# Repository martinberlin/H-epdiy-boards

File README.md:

## H-epdiy-boards list of open source variations

This boards where made with collaboration from Larry Bank and support from the [NLnet foundation](https://nlnet.nl).
Each variation is targeted for different needs. Intended for everyone to make their own custom modifications. For example: You don't need one of the eink connectors, or you don't need RTC, then just remove it from the Pick and place order. For more advanced users you can of course open the board in KiCad and reorganize stuff.
Pull Requests with variations or fixes are welcome.
Any of this circuits is made or designed with AI. They are all human reviewed and crafted carefully.

### epdiy-model-F

**What it provides:**

- A 40 pin connector for 16 bit Eink displays like ED103TC2 or ED103MC2
- 8 free GPIOs exposed if you don't use the 16 bit display
- A 34 pin connector for 8 bit Kindle like Eink displays (All the ED060***)
- Double USB-C connector w/built in USB only (no UART)
- A single BOOT / USER button (IO 0)
- An IR receiver TSOP341 (LCSC: C118303)
- RV3032 RTC with the INT pin connected to IO3 (RTC GPIO so you can wake up the MCU)
- Switchable QWIIC power so you can switch on a peripheral and cut it's power completely
- TP4056 battery charger

The IR is meant so you can make a simple Firmware and change the display content with  your TV remote.

How it looks like:

Some features like RTC and IR receiver:

[Full schematics PDF](epdiy-v7-model-F/v7-model-f_1.0.pdf)

## Links of interest

[How to read codes from IR Remote controls](https://bitbanksoftware.blogspot.com/2026/11/how-to-read-codes-from-many-ir-remote.html) Good article from Larry about receiving IR codes

[IDF Nec IR receive example](https://github.com/espressif/esp-idf/tree/master/examples/peripherals/rmt/ir_nec_transceiver) if you like ESP-IDF, just set the RX pin in **main/ir_nec_transceiver_main.c** to 43, make a **set-target esp32s3** and you are ready for an **idf.py flash monitor**

[sensoria board](https://fasani.de/2026/01/16/new-product-and-service-launched-sensoria/) A new product we are launching with a 5.2 inch variation of a FastEPD board

[FastEPD](https://github.com/bitbank2/FastEPD) An alternative and different library than epdiy to control raw parallel eink displays

If anyone makes a great Firmware to interact with an online image gallery and receive IR commands, then he can claim a 50% discount and free shipping in any of my boards sold on Tindie (I will send a Coupon)
PRE-REQUISITES: It should be code by hand with carefully clean code. Detection that is made with Claude or any other AI coding tool leaves you out of the contest.  You need to provide proof of commit history exactly for that reason.

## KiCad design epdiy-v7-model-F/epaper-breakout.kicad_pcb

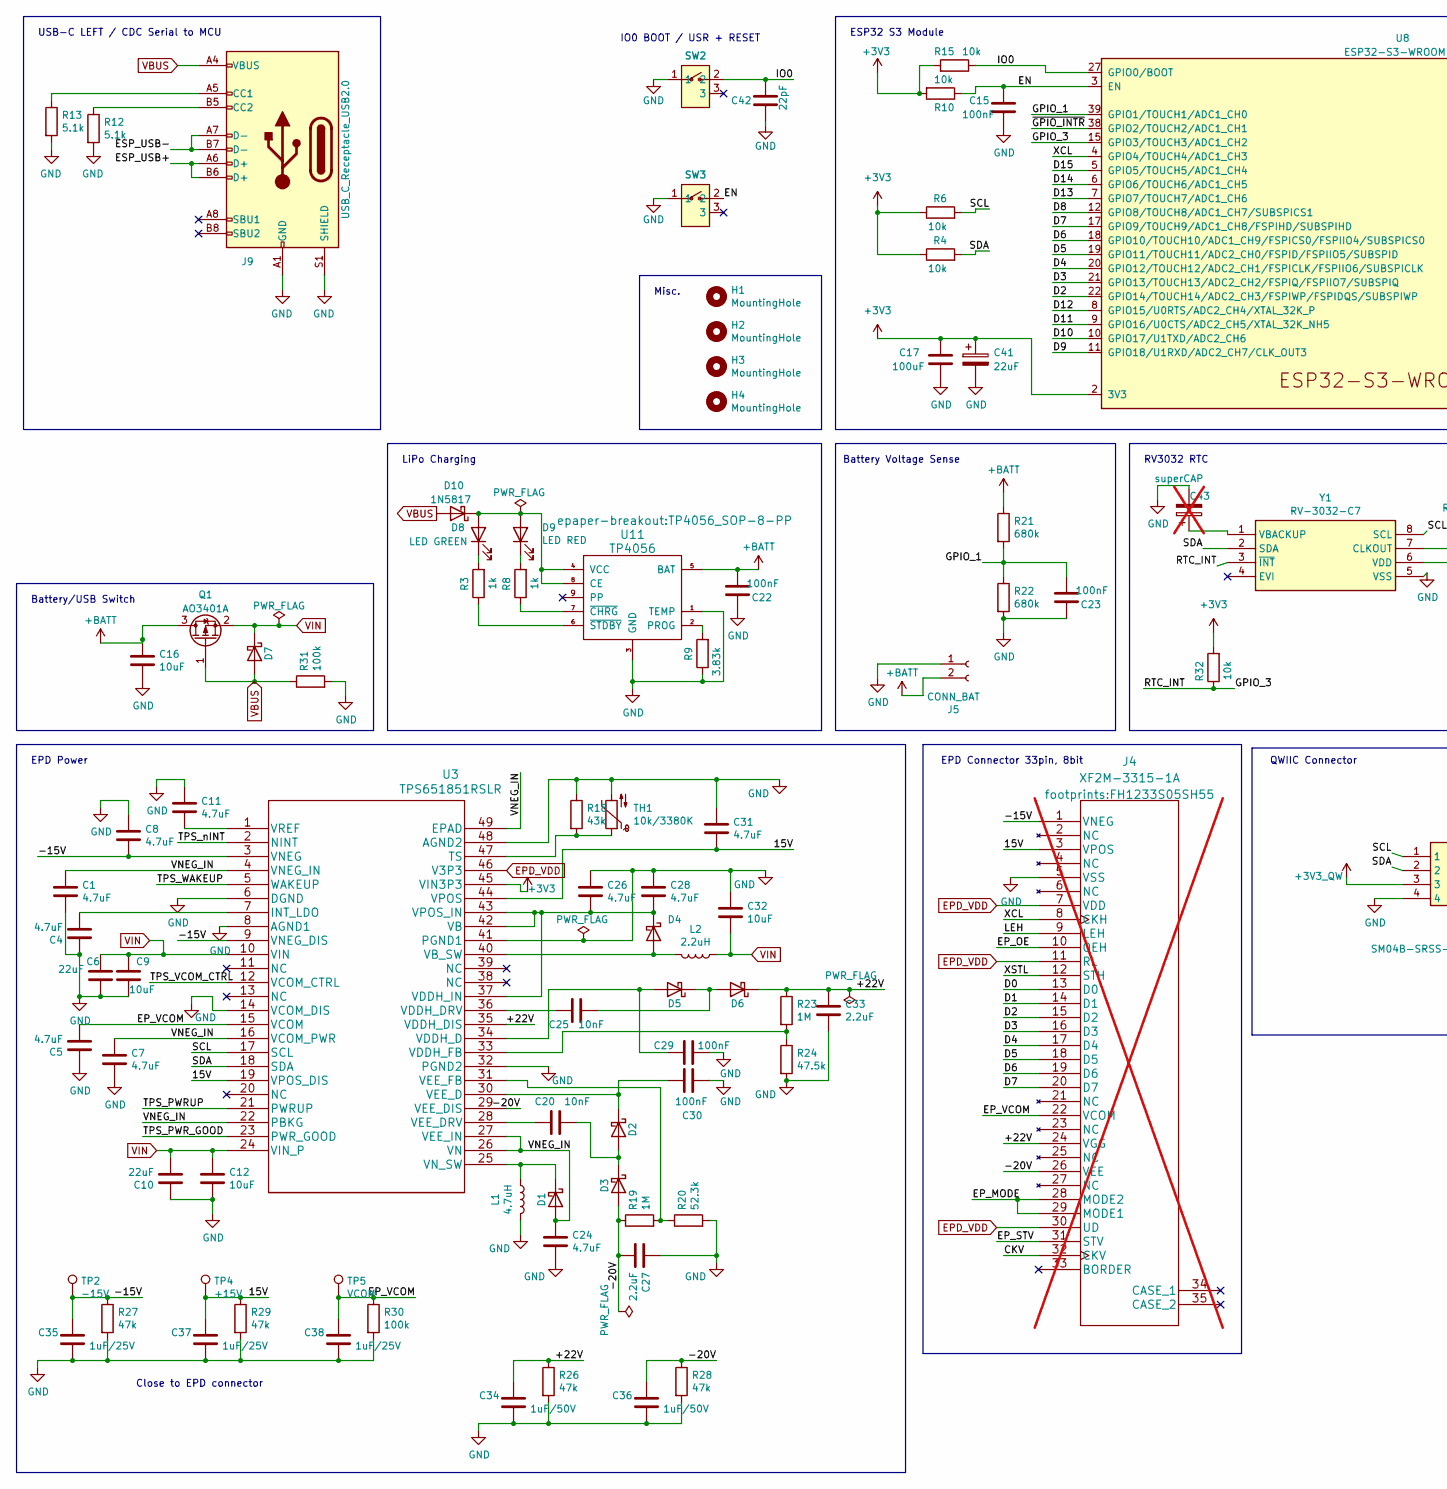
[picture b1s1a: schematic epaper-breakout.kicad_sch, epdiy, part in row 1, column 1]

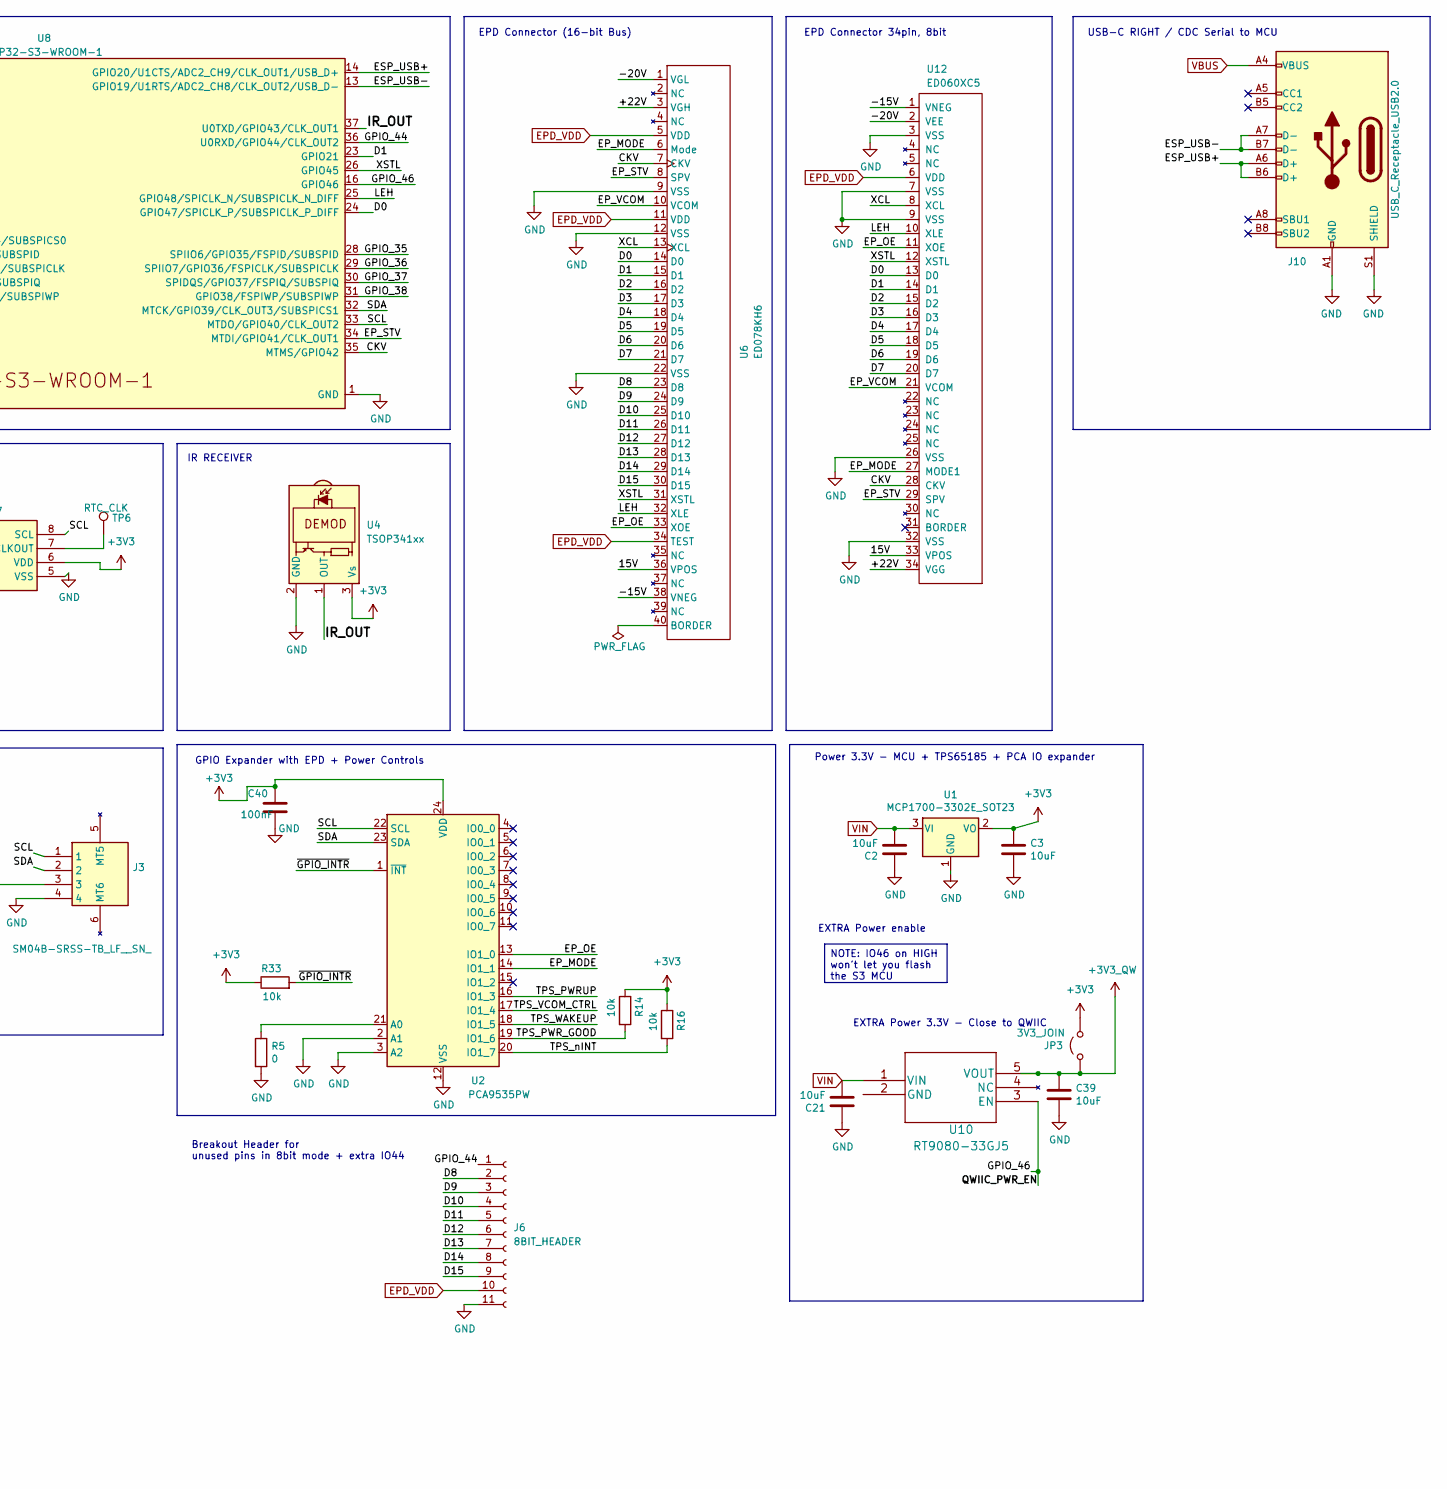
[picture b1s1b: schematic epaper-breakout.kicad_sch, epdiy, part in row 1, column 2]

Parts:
C1, C4, C5, C7, C8, C11, C24, C26, C28, C31: 4.7uF; C_0805_2012Metric; LCSC C1779
C2, C3, C9, C12, C16, C21, C32, C39: 10uF; C_0805_2012Metric; LCSC C15850
C6, C10: 22uF; C_0805_2012Metric; LCSC C45783
C15, C22, C23, C29, C30, C40: 100nF; C_0805_2012Metric; LCSC C49678
C17: 100uF; CP_EIA-3528-15_AVX-H; LCSC C16133
C20, C25: 10nF; C_0805_2012Metric; LCSC C1710
C27, C33: 2.2uF; C_0805_2012Metric; LCSC C49217
C34, C36: 1uF/50V; C_1206_3216Metric; LCSC C1848
C35, C37, C38: 1uF/25V; C_0805_2012Metric; LCSC C28323
C41: 22uF; C140412_CAP-SMD_L3.5-W2.8; LCSC C140412
C42: 22pF; C_0402_1005Metric; LCSC C5119318
C43: superCAP; C9900013866_SUPERCAP-TH_XH414HG; LCSC C9900013866; not fitted
D1, D2, D3, D4, D5, D6, D7: MBR0540; D_SOD-123; LCSC C21353
D8: LED GREEN; LED_0805_2012Metric; LCSC C2297
D9: LED RED; LED_0805_2012Metric; LCSC C84256
D10: 1N5817; D_SOD-123; LCSC C8598
H1, H2, H3, H4: MountingHole; MountingHole_2.2mm_M2
J3: SM04B-SRSS-TB_LF__SN_; QWIIC_SM04B-SRSS-TB_LFSN_; Manufacturer_Part_Number SM04B-SRSS-TB(LF)(SN); LCSC C160404
J4: XF2M-3315-1A; FH1233S05SH55; LCSC C597986; not fitted
J5: CONN_BAT; PinHeader_1x02_P2.54mm_Vertical
J6: 8BIT_HEADER; PinHeader_1x11_P2.54mm_Vertical
J9, J10: USB_C_Receptacle_USB2.0; USB_C_Receptacle_HRO_TYPE-C-31-M-12; LCSC C165948
JP3: 3V3_JOIN; SolderJumper-2_P1.3mm_Open_RoundedPad1.0x1.5mm
L1: 4.7uH; L_Taiyo-Yuden_NR-50xx_HandSoldering; LCSC C222947
L2: 2.2uH; L_Taiyo-Yuden_NR-40xx_HandSoldering; LCSC C92959
Q1: AO3401A; SOT-23; LCSC C15127
R3, R8: 1k; R_0603_1608Metric; LCSC C21190
R4, R6, R10, R14, R15, R16, R32, R33: 10k; R_0603_1608Metric; LCSC C25804
R5: 0; R_0603_1608Metric; LCSC C21189
R9: 3.83k; R_0603_1608Metric; LCSC C103591
R12, R13: 5.1k; R_0603_1608Metric; LCSC C23186
R18: 43k; R_0603_1608Metric; LCSC C23172
R19, R23: 1M; R_0603_1608Metric; LCSC C22935
R20: 52.3k; R_0603_1608Metric; LCSC C23196
R21, R22: 680k; R_0603_1608Metric; LCSC C25822
R24: 47.5k; R_0603_1608Metric; LCSC C25819
R26, R27, R28, R29: 47k; R_0603_1608Metric; LCSC C25819
R30, R31: 100k; R_0603_1608Metric; LCSC C25803
SW2, SW3: HX-3X6X3.5-CA-0.6-2.5N; C2686860_button_TC073B-H055-L1; LCSC C2686860
TH1: 10k/3380K; R_0603_1608Metric; LCSC C76589
TP2: -15V; TestPoint_Pad_D2.5mm
TP4: +15V; TestPoint_Pad_D2.5mm
TP5: VCOM; TestPoint_Pad_D2.5mm
TP6: RTC_CLK; TestPoint_Pad_1.0x1.0mm
U1: MCP1700-3302E_SOT23; SOT-23; LCSC C39051
U2: PCA9535PW; TSSOP-24_4.4x7.8mm_P0.65mm; LCSC C255606
U3: TPS651851RSLR; LCSC C139292
U4: TSOP341xx; Vishay_MOLD-3Pin; LCSC C118303
U6: ED078KH6; Hirose_FH12-40S-0.5SH_mirrored; LCSC C202114
U8: ESP32-S3-WROOM-1; LCSC C2913202
U10: RT9080-33GJ5; TSOT-23-5; LCSC C841192
U11: TP4056; TP4056_SOP-8-PP; LCSC C16581
U12: ED060XC5; X05A20H34G; LCSC C528053
Y1: RV-3032-C7; RV3032C7; Manufacturer_Part_Number RV-3032-C7; LCSC C5127802

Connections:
+3V3: C3.2, C17.1, C40.1, C41.1, JP3.2 (B), R4.1, R6.1, R10.2, R14.1, R15.2, R16.1, R32.2, R33.1, U1.2 (VO), U2.24 (VDD), U3.45 (VIN3P3), U4.3 (Vs), U8.2 (3V3), Y1.6 (VDD)
+3V3_QW: C39.2, J3.3, JP3.1 (A), U10.5 (VOUT)
+BATT: C16.2, C22.2, J5.2, Q1.3 (D), R21.1, U11.5 (BAT)
/15V: C31.2, C37.1, J4.3 (VPOS), R29.1, TP4.1 (1_1), U3.19 (VPOS_DIS), U3.44 (VPOS), U6.36 (VPOS), U12.33 (VPOS)
/+22V: C33.1, C34.1, D6.1 (K), J4.24 (VGG), R23.1, R26.1, U3.35 (VDDH_DIS), U6.3 (VGH), U12.34 (VGG)
/-15V: C8.2, C35.1, J4.1 (VNEG), R27.1, TP2.1 (1_1), U3.3 (VNEG), U3.9 (VNEG_DIS), U6.38 (VNEG), U12.1 (VNEG)
/-20V: C27.2, C36.1, D3.2 (A), J4.26 (VEE), R19.1, R28.1, U3.29 (VEE_DIS), U6.1 (VGL), U12.2 (VEE)
/CKV: J4.32 (CKV), U6.7 (CKV), U8.35 (MTMS/GPIO42), U12.28 (CKV)
/D0: J4.13 (D0), U6.14 (D0), U8.24 (GPIO47/SPICLK_P/SUBSPICLK_P_DIFF), U12.13 (D0)
/D1: J4.14 (D1), U6.15 (D1), U8.23 (GPIO21), U12.14 (D1)
/D2: J4.15 (D2), U6.16 (D2), U8.22 (GPIO14/TOUCH14/ADC2_CH3/FSPIWP/FSPIDQS/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), U12.15 (D2)
/D3: J4.16 (D3), U6.17 (D3), U8.21 (GPIO13/TOUCH13/ADC2_CH2/FSPIQ/FSPIIO7/S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), U12.16 (D3)
/D4: J4.17 (D4), U6.18 (D4), U8.20 (GPIO12/TOUCH12/ADC2_CH1/FSPICLK/FSPIIO6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), U12.17 (D4)
/D5: J4.18 (D5), U6.19 (D5), U8.19 (GPIO11/TOUCH11/ADC2_CH0/FSPID/FSPIIO5/S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), U12.18 (D5)
/D6: J4.19 (D6), U6.20 (D6), U8.18 (GPIO10/TOUCH10/ADC1_CH9/FSPICS0/FSPIIO4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), U12.19 (D6)
/D7: J4.20 (D7), U6.21 (D7), U8.17 (GPIO9/TOUCH9/ADC1_CH8/FSPIHD/SUBSPIHD), U12.20 (D7)
/D8: J6.2, U6.23 (D8), U8.12 (GPIO8/TOUCH8/ADC1_CH7/SUBSPICS1)
/D9: J6.3, U6.24 (D9), U8.11 (GPIO18/U1RXD/ADC2_CH7/CLK_OUT3)
/D10: J6.4, U6.25 (D10), U8.10 (GPIO17/U1TXD/ADC2_CH6)
/D11: J6.5, U6.26 (D11), U8.9 (GPIO16/U0CTS/ADC2_CH5/XTAL_32K_NH5)
/D12: J6.6, U6.27 (D12), U8.8 (GPIO15/U0RTS/ADC2_CH4/XTAL_32K_P)
/D13: J6.7, U6.28 (D13), U8.7 (GPIO7/TOUCH7/ADC1_CH6)
/D14: J6.8, U6.29 (D14), U8.6 (GPIO6/TOUCH6/ADC1_CH5)
/D15: J6.9, U6.30 (D15), U8.5 (GPIO5/TOUCH5/ADC1_CH4)
/EN: C15.1, R10.1, SW3.2, U8.3 (EN)
/EP_MODE: J4.28 (MODE2), J4.29 (MODE1), U2.14 (IO1_1), U6.6 (Mode), U12.27 (MODE1)
/EP_OE: J4.10 (OEH), U2.13 (IO1_0), U6.33 (XOE), U12.11 (XOE)
/EP_STV: J4.31 (STV), U6.8 (SPV), U8.34 (MTDI/GPIO41/CLK_OUT1), U12.29 (SPV)
/EP_VCOM: C5.2, C38.1, J4.22 (VCOM), R30.1, TP5.1 (1_1), U3.15 (VCOM), U6.10 (VCOM), U12.21 (VCOM)
/ESP_USB+: J9.A6 (D+), J9.B6 (D+), J10.A6 (D+), J10.B6 (D+), U8.14 (GPIO20/U1CTS/ADC2_CH9/CLK_OUT1/USB_D+)
/ESP_USB-: J9.A7 (D-), J9.B7 (D-), J10.A7 (D-), J10.B7 (D-), U8.13 (GPIO19/U1RTS/ADC2_CH8/CLK_OUT2/USB_D-)
/GPIO_1: C23.2, R21.2, R22.1, U8.39 (GPIO1/TOUCH1/ADC1_CH0)
/GPIO_3: R32.1, U8.15 (GPIO3/TOUCH3/ADC1_CH2), Y1.3 (~INT)
/GPIO_35: U8.28 (SPIIO6/GPIO35/FSPID/SUBSPID)
/GPIO_36: U8.29 (SPIIO7/GPIO36/FSPICLK/SUBSPICLK)
/GPIO_37: U8.30 (SPIDQS/GPIO37/FSPIQ/SUBSPIQ)
/GPIO_38: U8.31 (GPIO38/FSPIWP/SUBSPIWP)
/GPIO_44: J6.1, U8.36 (U0RXD/GPIO44/CLK_OUT2)
/GPIO_46: U8.16 (GPIO46), U10.3 (EN)
/IO0: C42.2, R15.1, SW2.2, U8.27 (GPIO0/BOOT)
/IR_OUT: U4.1 (OUT), U8.37 (U0TXD/GPIO43/CLK_OUT1)
/LEH: J4.9 (LEH), U6.32 (XLE), U8.25 (GPIO48/SPICLK_N/SUBSPICLK_N_DIFF), U12.10 (XLE)
/SCL: J3.1, R6.2, U2.22 (SCL), U3.17 (SCL), U8.33 (MTDO/GPIO40/CLK_OUT2), Y1.8 (SCL)
/SDA: J3.2, R4.2, U2.23 (SDA), U3.18 (SDA), U8.32 (MTCK/GPIO39/CLK_OUT3/SUBSPICS1), Y1.2 (SDA)
/TPS_PWRUP: U2.16 (IO1_3), U3.21 (PWRUP)
/TPS_PWR_GOOD: R14.2, U2.19 (IO1_6), U3.23 (PWR_GOOD)
/TPS_VCOM_CTRL: U2.17 (IO1_4), U3.12 (VCOM_CTRL)
/TPS_WAKEUP: U2.18 (IO1_5), U3.5 (WAKEUP)
/TPS_nINT: R16.2, U2.20 (IO1_7), U3.2 (NINT)
/VNEG_IN: C1.1, C7.1, C24.1, D1.2 (A), U3.4 (VNEG_IN), U3.16 (VCOM_PWR), U3.22 (PBKG), U3.26 (VN), U3.27 (VEE_IN), U3.49 (EPAD)
/XCL: J4.8 (CKH), U6.13 (XCL), U8.4 (GPIO4/TOUCH4/ADC1_CH3), U12.8 (XCL)
/XSTL: J4.12 (STH), U6.31 (XSTL), U8.26 (GPIO45), U12.12 (XSTL)
/~GPIO_INTR: R33.2, U2.1 (~INT), U8.38 (GPIO2/TOUCH2/ADC1_CH1)
EPD_VDD: J4.7 (VDD), J4.11 (RL), J4.30 (UD), J6.10, U3.46 (V3P3), U6.5 (VDD), U6.11 (VDD), U6.34 (TEST), U12.6 (VDD)
unnamed: D1.1 (K), L1.1, U3.25 (VN_SW)
unnamed: C20.1, D2.2 (A), D3.1 (K)
unnamed: C30.1, D2.1 (K), U3.30 (VEE_D)
unnamed: D4.2 (A), L2.2, U3.40 (VB_SW)
unnamed: C26.2, C28.2, D4.1 (K), U3.37 (VDDH_IN), U3.42 (VB), U3.43 (VPOS_IN)
unnamed: C29.2, D5.2 (A), U3.34 (VDDH_D)
unnamed: C25.1, D5.1 (K), D6.2 (A)
unnamed: D8.1 (K), R3.2
unnamed: D9.1 (K), R8.2
unnamed: D8.2 (A), D9.2 (A), D10.1 (K), U11.4 (VCC), U11.8 (CE)
unnamed: J9.A5 (CC1), R13.1
unnamed: J9.B5 (CC2), R12.1
unnamed: R5.1, U2.21 (A0)
unnamed: C4.2, U3.7 (INT_LDO)
unnamed: R18.2, TH1.1, U3.47 (TS)
unnamed: C25.2, U3.36 (VDDH_DRV)
unnamed: R23.2, R24.1, U3.33 (VDDH_FB)
unnamed: C20.2, U3.28 (VEE_DRV)
unnamed: R19.2, R20.1, U3.31 (VEE_FB)
unnamed: C11.2, U3.1 (VREF)
unnamed: R9.2, U11.2 (PROG)
unnamed: R8.1, U11.7 (~CHRG)
unnamed: R3.1, U11.6 (~STDBY)
unnamed: TP6.1 (1_1), Y1.7 (CLKOUT)
unnamed: C43.1, Y1.1 (VBACKUP)
VBUS: D7.2 (A), D10.2 (A), J9.A4 (VBUS), J9.A9 (VBUS), J9.B4 (VBUS), J9.B9 (VBUS), J10.A4 (VBUS), J10.A9 (VBUS), J10.B4 (VBUS), J10.B9 (VBUS), Q1.1 (G), R31.1
VIN: C2.1, C6.2, C9.1, C10.2, C12.1, C21.1, C32.2, D7.1 (K), L2.1, Q1.2 (S), U1.3 (VI), U3.10 (VIN), U3.24 (VIN_P), U10.1 (VIN)

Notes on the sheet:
Battery Voltage Sense
QWIIC Connector
Misc.
USB-C RIGHT / CDC Serial to MCU
IR RECEIVER
EPD Power
GPIO Expander with EPD + Power Controls
EPD Connector (16-bit Bus)
ESP32 S3 Module
USB-C LEFT / CDC Serial to MCU
EXTRA Power enable
Power 3.3V - MCU + TPS65185 + PCA IO expander
EPD Connector 33pin, 8bit
Battery/USB Switch
RV3032 RTC
EXTRA Power 3.3V - Close to QWIIC
EPD Connector 34pin, 8bit
Breakout Header for unused pins in 8bit mode + extra IO44
IO0 BOOT / USR + RESET
LiPo Charging
Close to EPD connector
NOTE: IO46 on HIGH won't let you flash the S3 MCU

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
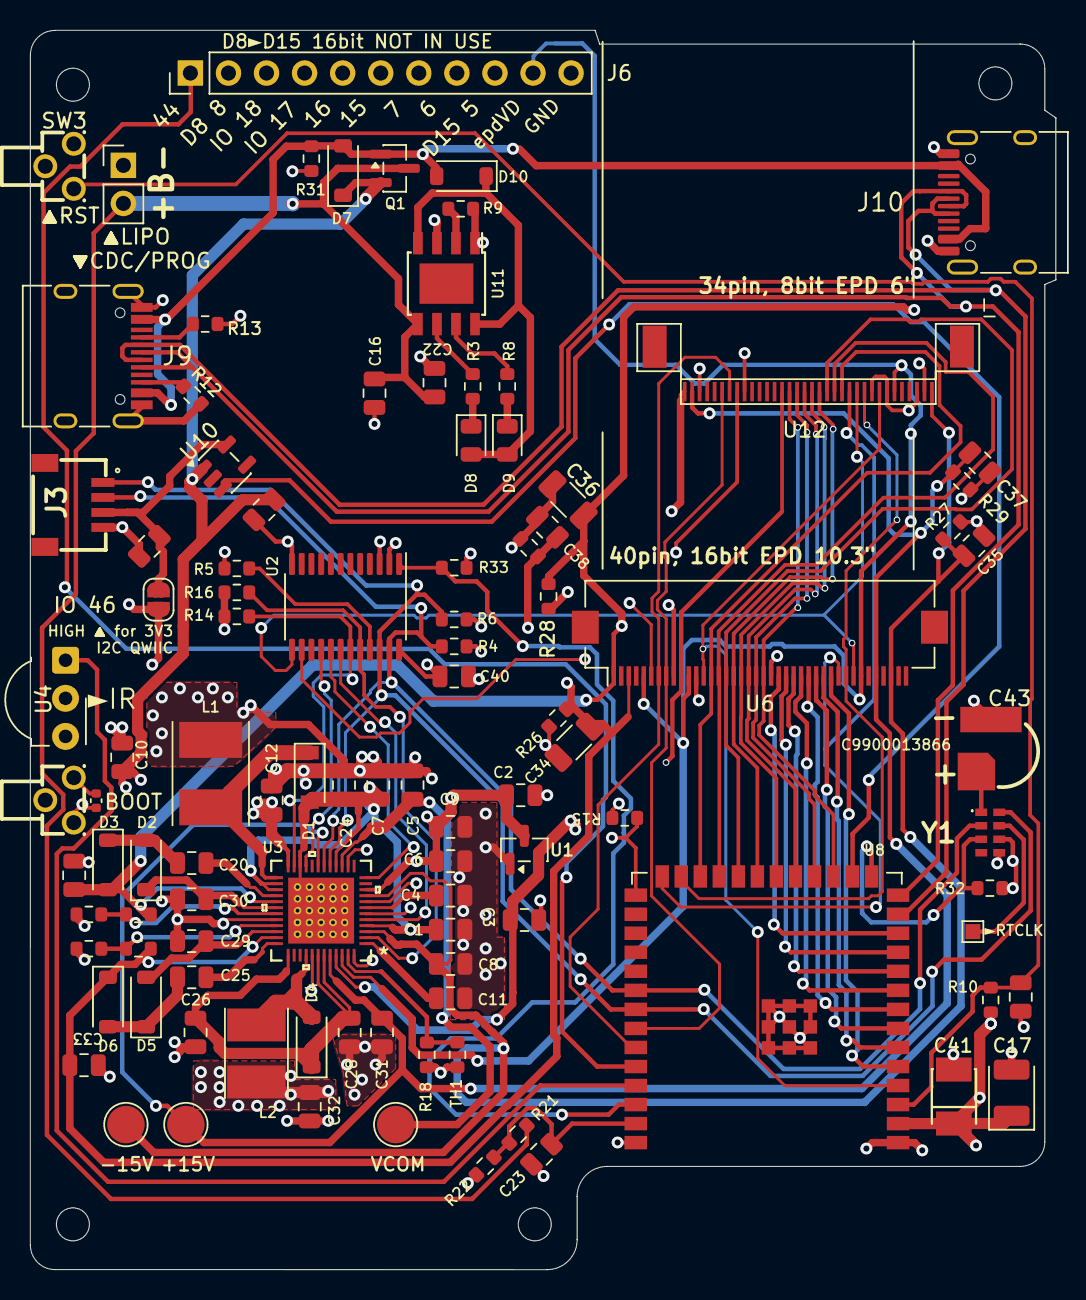
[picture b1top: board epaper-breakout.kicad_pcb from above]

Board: 4 copper layers, 68.4 x 82.7 mm, 106 parts (0 on the bottom side), 78 nets.

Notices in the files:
epdiy-v7-model-F/epaper-breakout.kicad_sch:
License: CC-BY-SA-4.0
parts and their libraries:
Copyright 2016 Accelerated Designs. All rights reserved.
